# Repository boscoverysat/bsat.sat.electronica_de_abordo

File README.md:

# SAT Electrónica de Abordo

### Este repositorio ha sido descontinuado.

La información relativa a los elementos electrónicos del satélite podrán encontrarse en los siguientes enlaces:

- [Onboard Computer (OBC)](https://github.com/boscoverysat/bsat.sat.electronica.onboard_computer)
- [Electric Power System (EPS)](https://github.com/boscoverysat/bsat.sat.electronica.electric_power_system)
- [Communications (COMM)](https://github.com/boscoverysat/bsat.sat.electronica.communications)
- [Librerías](https://github.com/boscoverysat/bsat.sat.electronica.librerias)

### Licencia

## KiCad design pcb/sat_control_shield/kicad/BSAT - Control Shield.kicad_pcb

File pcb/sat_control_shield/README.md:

# SAT Control Shield

## Resumen

Esta sección del repositorio contiene el circuito electrónico y el diseño de placa de circuito impreso para el sistema de control del satélite.

El actual diseño electrónico se ha llevado a cabo mediante el software **KiCAD** e incluye en una misma placa, el núcleo de procesamiento del
satélite (formado por un Arduino Nano v3.0), los sensores de inercia y orientación, así como un único sensor de temperatura, los pines necesarios
para la conexión de cuatro sensores de intensidad luminosa y el módulo de transmisión RF a 433MHz.

## Contenido actual de la Shield

La PCB cuenta con unas dimensiones de 77 x 77 mm, realizada en base de fibra de vidrio y una única capa de cobre, disponiendo de cuatro orificios
de fijación, para el chasis del satélite, ubicados en las esquinas de la placa.

Actualmente la placa cuenta con una alimentación simple que proviene desde la shield de alimentación. De este modo, a la entrada de la placa disponemos
de un nivel de tensión de entre 7,5VDC y 8,4VDC, dependiendo del nivel de carga que tengan las baterías.

Con este nivel de voltaje se proporciona energía directamente a la unidad de control del satélite, formada por el Arduino Nano v3.0. A partir de él,
empleamos las salidas estabilizadas de 5VDC y 3,3VDC para alimentar al resto de elementos del circuito.

De este modo, el giroscopico (`HPU6000`), el acelerómetro (`HMC5883L`), el sensor de temperatura (`HTU21D`) y los sensores de luminosidad (`BH1750`) se
encuentran alimentados a 3,3VDC.

Por otro lado, el transmisor de RF (`CDT-88`) y el multiplexor de I2C (`74HC4052E`) se encuentran alimentados a 5VDC.

Todos los sensores presentes en la placa, se comunican con el Arduino a través del bus I2C. Por esta razón y dado que en el diseño se emplean múltiple
sensores del mismo modelo que vienen con la dirección de comunicación fijada por hardware, ha sido necesario emplear el circuito integrado `74HC4052E`,
encargado de multiplexar la señal SDA del I2C.

**NOTA:** La **multiplexación** de la señal **SDA** del bus **I2C** mediante el circuito integrado `74HC4052E` aún se encuentra en **fase experimental**.

## Fallos detectados

Aún no se han detectado fallos para el diseño actual.

## Propuestas de mejora

- Confirmar el correcto funcionamiento de la multiplexación del canal SDA del bus I2C mediante el uso del circuito integrado `74HC4052E`.
- Multiplexar la señal SDA para los sensores de intensidad luminosa.
- Multiplexar la señal SDA para los sensores de temperatura.
- Obtener lecturas de los niveles de tensión proporcionados por las placas solares dispuestas en las caras del satélite.
- Obtener lecturas de los niveles de tensión proporcionados por las baterías del sistema de alimentación.

#### Diseño PCB

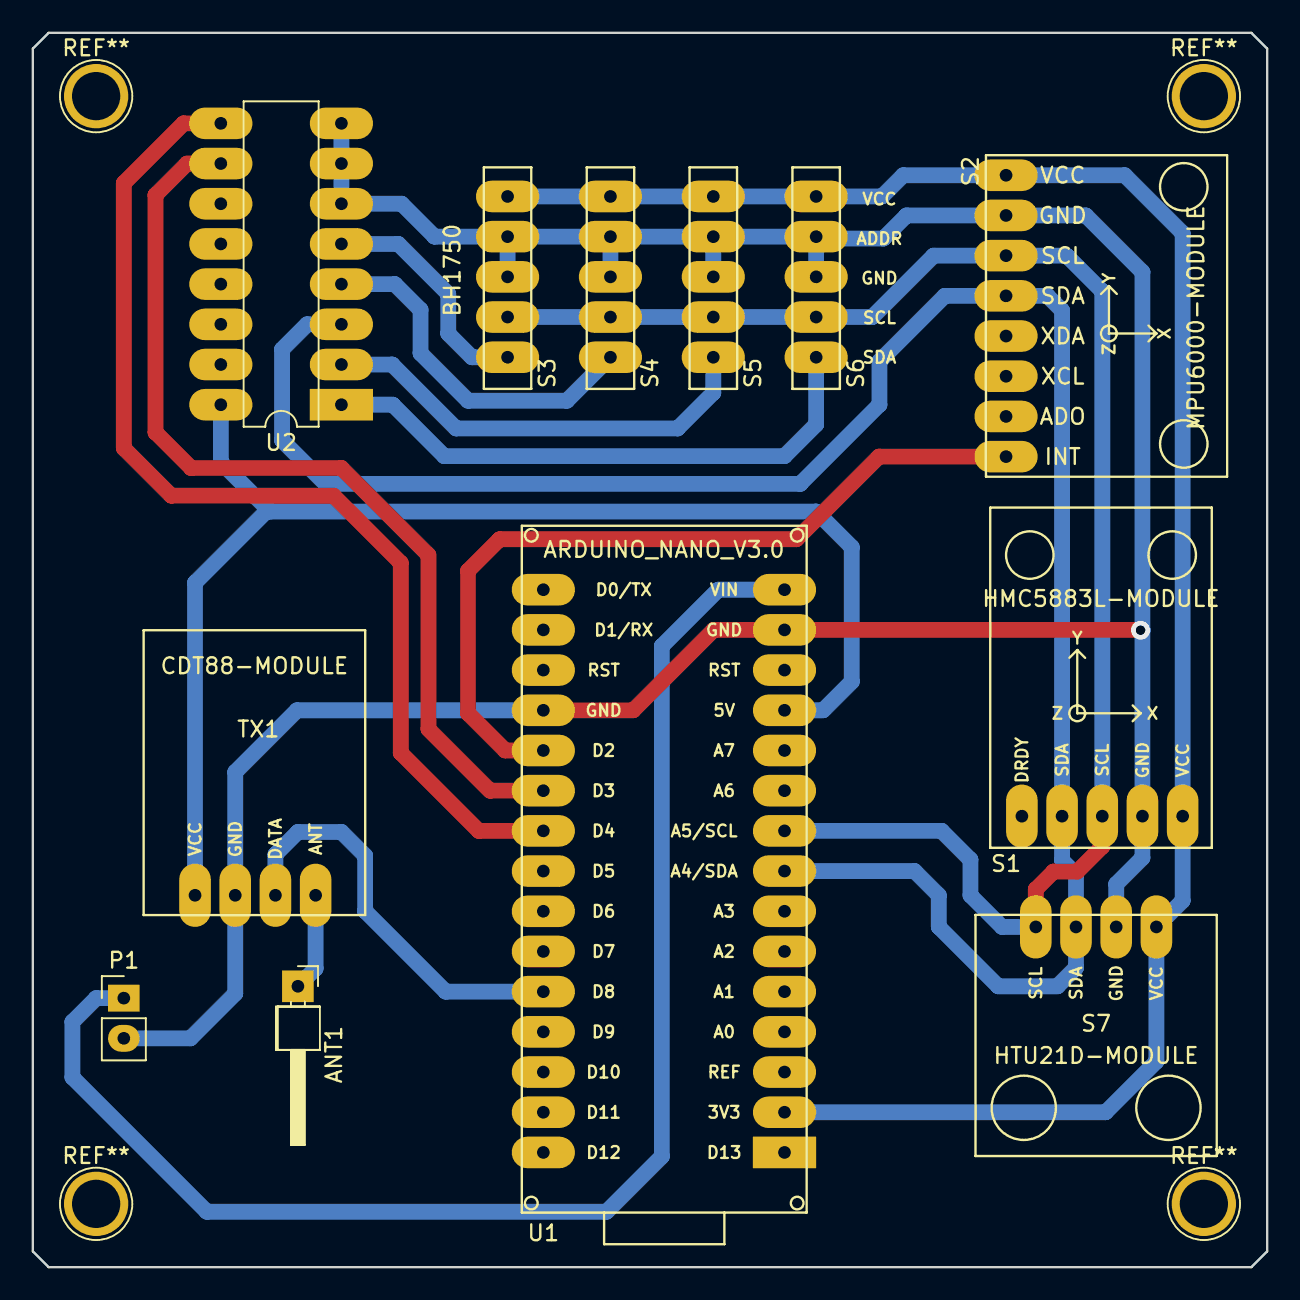
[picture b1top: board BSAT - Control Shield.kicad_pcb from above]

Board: 2 copper layers, 78.0 x 78.0 mm, 12 parts (0 on the bottom side), 15 nets.

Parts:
ANT1: ANTENNA-1; Pin_Header_Angled_1x01_Pitch2.54mm
P1: POWER; Pin_Header_Straight_1x02_Pitch2.54mm
S1: HMC5883L-MODULE; HMC5883L
S2: MPU6000-MODULE; MPU-6000
S3: BH1750; BH1750-MODULE
S4, S5, S6: BH1750-MODULE
S7: HTU21D-MODULE
TX1: CDT88-MODULE; CDT-88
U1: ARDUINO_NANO_V3.0
U2: 74HC4052E; DIP-16_W7.62mm_LongPads

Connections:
+3V3: S1.5, S2.1, S3.5, S4.5, S5.5, S6.5, S7.1, U1.2
+5V: TX1.1, U1.12, U2.16
/GYRO_INT: S2.8, U1.20
/LS_SELECT_0: U1.21, U2.10
/LS_SELECT_1: U1.22, U2.9
/SCL: S1.3, S2.3, S3.2, S4.2, S5.2, S6.2, S7.4, U1.9
/SDA: S1.2, S2.4, S7.3, U1.8, U2.3
/SDA_LS_SIDE1: S3.1, U2.5
/SDA_LS_SIDE2: S4.1, U2.4
/SDA_LS_SIDE3: S5.1, U2.2
/SDA_LS_SIDE4: S6.1, U2.1
GNDREF: P1.2, S1.4, S2.2, S3.3, S3.4, S4.3, S4.4, S5.3, S5.4, S6.3, S6.4, S7.2, TX1.2, U1.14, U1.19, U2.6, U2.7, U2.8
unnamed: ANT1.1, TX1.4
RADIO_DATA: TX1.3, U1.26
VCC: P1.1, U1.15

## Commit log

2016-06-08 chore(repositorio): Repositorio inicializado.
2016-06-08 feat(receptor-rf-430mhz): Diseño del receptor de pruebas realizado.
2016-06-08 feat(battery-shield): Diseño del módulo de alimentación realizado.
2016-06-08 feat(battery-shield): Diseño del módulo de control realizado.
2016-06-08 feat(battery-shield): Diseño del módulo de transmisiones realizado.
2016-06-08 docs(readme): Archivo README.md principal actualizado.
2016-06-08 docs(battery-shield): Añadidos documentos de guía y datasheets al repositorio.
2016-06-08 feat(kicad-bsat-lib): Creada la librería de componentes electrónicos para KiCAD, empleados en el satélite.
2016-06-08 feat(battery-shield): Rediseño de la placa mediante el programa KiCAD.
2016-06-08 feat(control-shield): Rediseño de la placa mediante el programa KiCAD.
2016-06-08 docs(readme): Archivos README.md actualizados.
2016-06-11 docs(datasheet): Datasheet de los componentes NDS8435 y NEC-PS2911-1 añadidos.
2016-06-11 feat(kicad-bsat-lib): Componentes NDS8435 y NEC-PS2911-1 añadidos.
2016-06-11 feat(battery-shield): Esquema reorganizado y optoacoplador añadido para el enable/disable del cargador.
2017-02-07 refactor(battery-shield): Rediseño de la placa empleando el regulador de carga MAX1873.
2017-02-07 refactor(control-shield): Rediseño de la placa y corrección de error en la conmutación entre sensores de intensidad luminosa.
2017-02-08 chore(battery-shield): Organizar archivos del diseño.
2017-02-08 chore(control-shield): Actualizar el diseño de pads para los componentes de la control-shield.
2017-05-13 refactor(control-shield): Rediseñar el diagrama de pistas para obtener una placa de doble cara.
2017-05-13 feat(control-shield): Generar los archivos Gerber para el fresado de la placa de control.
2017-05-13 feat(control-shield): Generar los archivos GCode para el fresado de la placa de control.
2017-05-14 docs(readme): Actualizar el contenido del archivo README.md.

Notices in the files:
README.md:
Licencia:
[Creaive Commons 4.0 logo](http://creativecommons.org/licenses/by-nc-sa/4.0/)
